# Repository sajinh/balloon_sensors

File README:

On the balloon we aim for data logging instead of real-time transmission. The
balloon is to be brought down periodically to collect data. Data is collected
using an onboard uLog.

We use BMP085 to measure absolute pressure. This also provides the temperature
value. BMP085 uses a Two Wire protocol for data transmission and operates
at 3.3V.  Analog Pin 5 is used for SCL and Analog Pin 4 for SDA.

We use HH10D to measure relative humidity. A Two Wire interface is needed
to read calibration coefficients from its onboard EEPROM. However we 
read it for once, record it in the sensor code, and never use the Two Wire
interface thereafter. The data is output as encoded frequency and output through
the middle pin.

uLog is a Serial Logger. Data is send through the TX line of the microcontroller

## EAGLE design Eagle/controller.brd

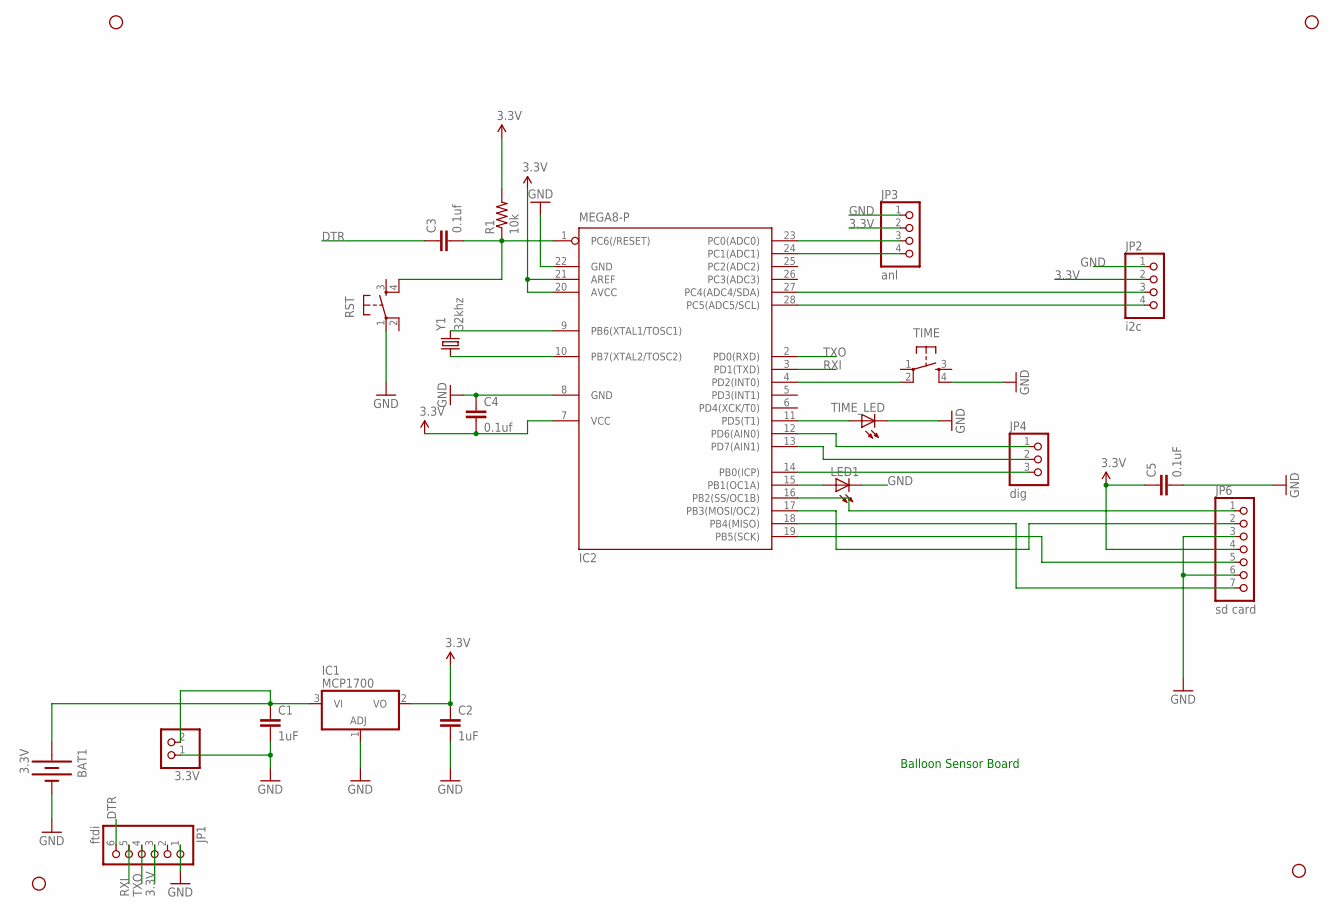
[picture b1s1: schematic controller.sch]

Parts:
3.3V: PINHD-1X2; 1X02
BAT1: 3.3V; BATTCON_245MM
C1, C2: 1uF; CAP-PTH-5MM
C3, C4: 0.1uf; CAP-PTH-5MM
C5: 0.1uF; CAP-PTH-5MM
IC1: MCP1700; TO92
IC2: MEGA8-P; DIL28-3
JP1: ftdi; 1X06
JP2: i2c; 1X04
JP3: anl; 1X04
JP4: dig; 1X03
JP6: sd card; 1X07
LED1: LED5MM
R1: 10k; AXIAL-0.5
RST: TAC_SWITCHPTH; TACTILE-PTH
STANDOFF1, STANDOFF2, STANDOFF3, STANDOFF4: STAND-OFF
TIME: TAC_SWITCHPTH; TACTILE-PTH
TIME_LED: LED5MM
Y1: 32khz; TC26H

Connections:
3.3V: C2.1, C4.2, C5.1, IC1.2 (VO), IC2.7 (VCC), IC2.20 (AVCC), IC2.21 (AREF), JP1.3, JP2.2, JP3.2, JP6.4, R1.P$2 (2)
+: 3.3V.2, BAT1.1 (+), C1.1, IC1.3 (VI)
DTR: C3.1, JP1.6
GND: 3.3V.1, BAT1.2 (-), C1.2, C2.2, C4.1, C5.2, IC1.1 (ADJ), IC2.8 (GND), IC2.22 (GND), JP1.1, JP2.1, JP3.1, JP6.3, JP6.6, LED1.K (C), RST.1, TIME.4, TIME_LED.K (C)
unnamed: C3.2, IC2.1 (PC6(/RESET)), R1.P$1 (1), RST.4
unnamed: IC2.15 (PB1(OC1A)), LED1.A
unnamed: IC2.28 (PC5(ADC5/SCL)), JP2.4
unnamed: IC2.9 (PB6(XTAL1/TOSC1)), Y1.2
unnamed: IC2.10 (PB7(XTAL2/TOSC2)), Y1.1
unnamed: IC2.14 (PB0(ICP)), JP4.3
unnamed: IC2.4 (PD2(INT0)), TIME.2
unnamed: IC2.13 (PD7(AIN1)), JP4.2
unnamed: IC2.27 (PC4(ADC4/SDA)), JP2.3
unnamed: IC2.24 (PC1(ADC1)), JP3.4
unnamed: IC2.23 (PC0(ADC0)), JP3.3
unnamed: IC2.12 (PD6(AIN0)), JP4.1
unnamed: IC2.11 (PD5(T1)), TIME_LED.A
unnamed: IC2.19 (PB5(SCK)), JP6.5
unnamed: IC2.18 (PB4(MISO)), JP6.7
unnamed: IC2.16 (PB2(SS/OC1B)), JP6.1
unnamed: IC2.17 (PB3(MOSI/OC2)), JP6.2
RXI: IC2.3 (PD1(TXD)), JP1.5
TXO: IC2.2 (PD0(RXD)), JP1.4

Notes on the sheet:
Balloon Sensor Board

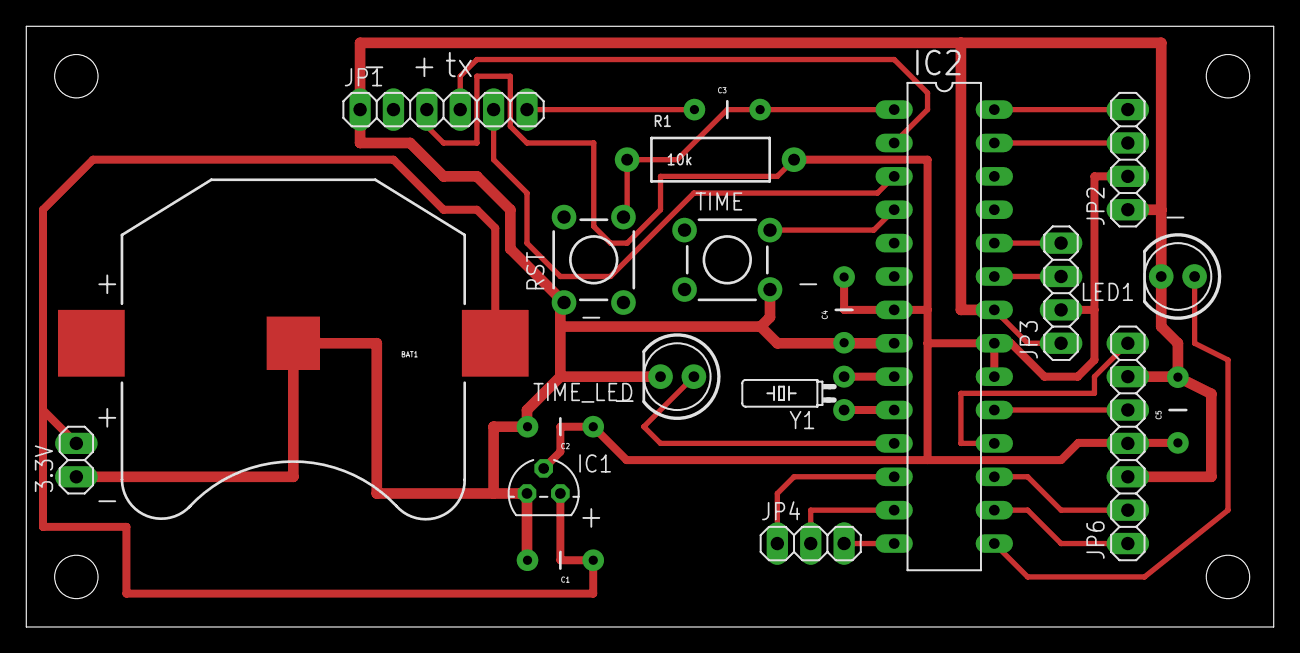
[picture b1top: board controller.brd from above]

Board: 2 copper layers, 94.9 x 45.7 mm, 24 parts (0 on the bottom side), 23 nets.

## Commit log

2012-07-11 working version
2012-07-11 README
2012-11-28 eagle files
2012-12-04 new Eagle files

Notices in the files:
parts and their libraries:
SparkFun-Electromechanical: Licensing: CC v3.0 Share-Alike You are welcome to use this library for commercial purposes.
